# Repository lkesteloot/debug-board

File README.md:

# Debug board

Breakout daughterboard for four debug LEDs. KiCAD schematic and PCB.

This was my first PCB, as a test to OSHPark.

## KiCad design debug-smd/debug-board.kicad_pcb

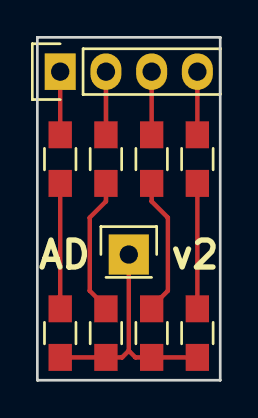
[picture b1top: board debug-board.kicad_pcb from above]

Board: 2 copper layers, 10.2 x 19.0 mm, 10 parts (0 on the bottom side), 9 nets.

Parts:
D1, D2, D3, D4: LED; R_0805_HandSoldering
P1: CONN_01X04; Pin_Header_Straight_1x04
P2: CONN_01X01; Pin_Header_Straight_1x01
R1, R2, R3, R4: 220; R_0805_HandSoldering

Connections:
GND: P2.1, R1.2, R2.2, R3.2, R4.2
unnamed: D1.1, R1.1
unnamed: D1.2, P1.1
unnamed: D2.1, R2.1
unnamed: D2.2, P1.2
unnamed: D3.1, R3.1
unnamed: D3.2, P1.3
unnamed: D4.1, R4.1
unnamed: D4.2, P1.4

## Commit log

2015-12-31 Initial revision.
2015-12-31 Layout PCB.
2015-12-31 Finish PCB.
2016-01-18 Split into TH and SMD.
2016-01-25 Convert to SMD.
2019-01-30 Various old updates.
